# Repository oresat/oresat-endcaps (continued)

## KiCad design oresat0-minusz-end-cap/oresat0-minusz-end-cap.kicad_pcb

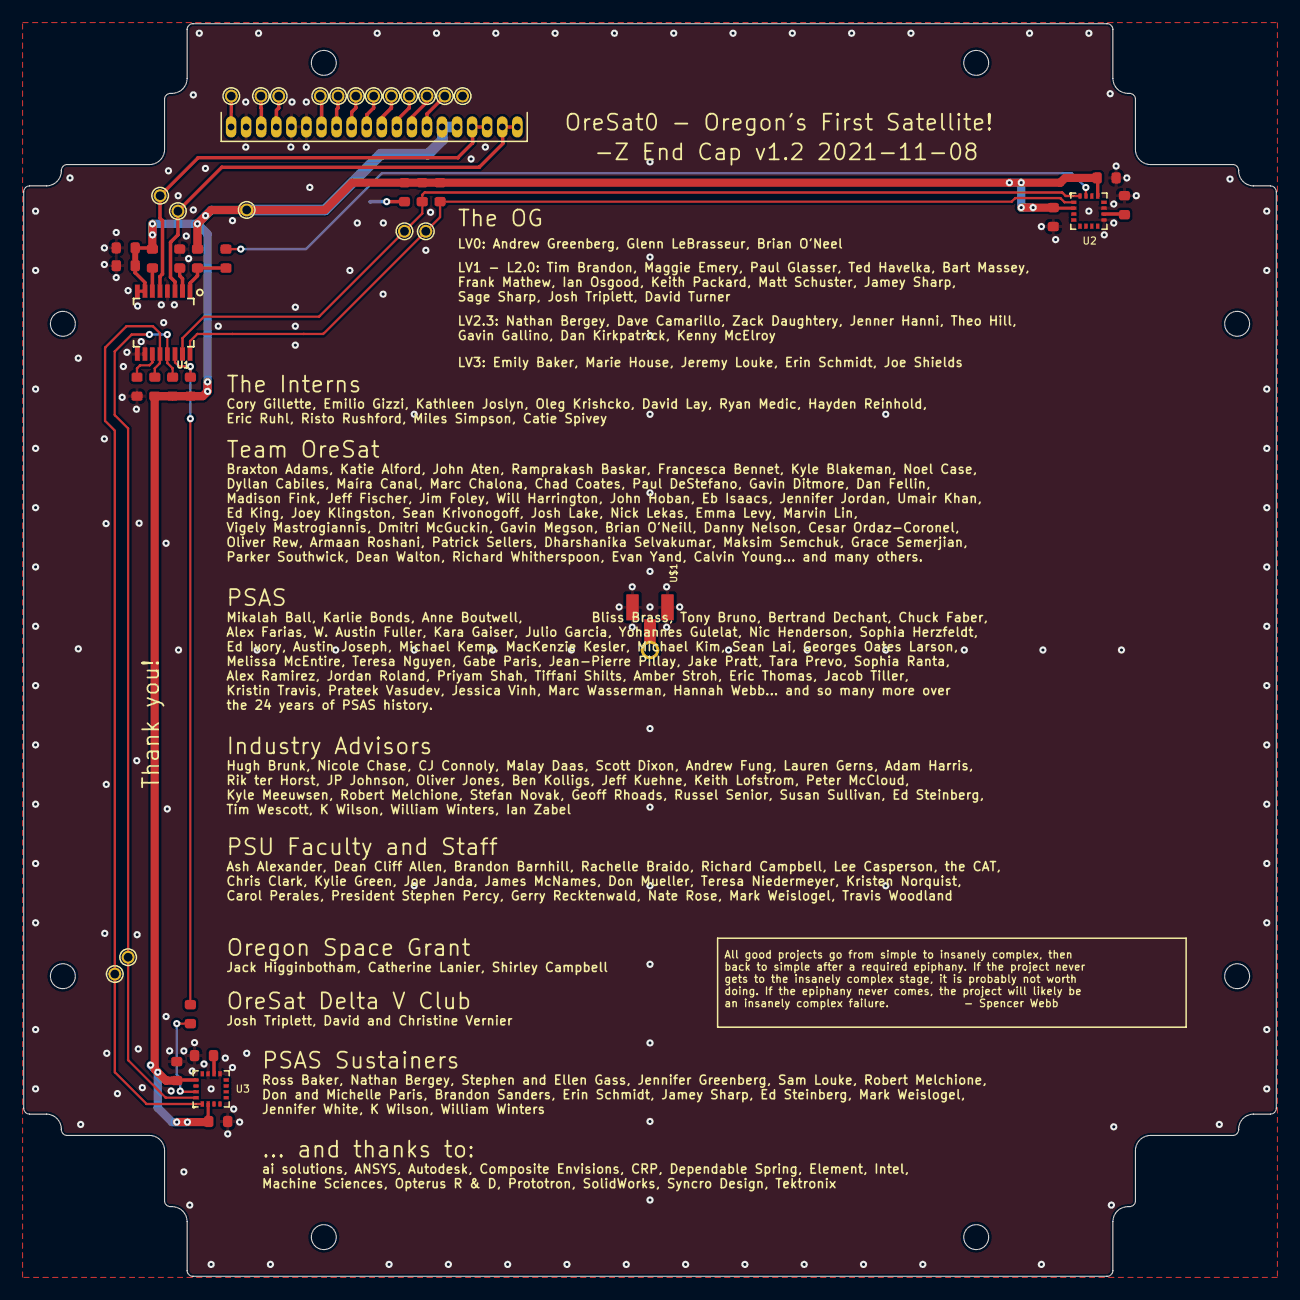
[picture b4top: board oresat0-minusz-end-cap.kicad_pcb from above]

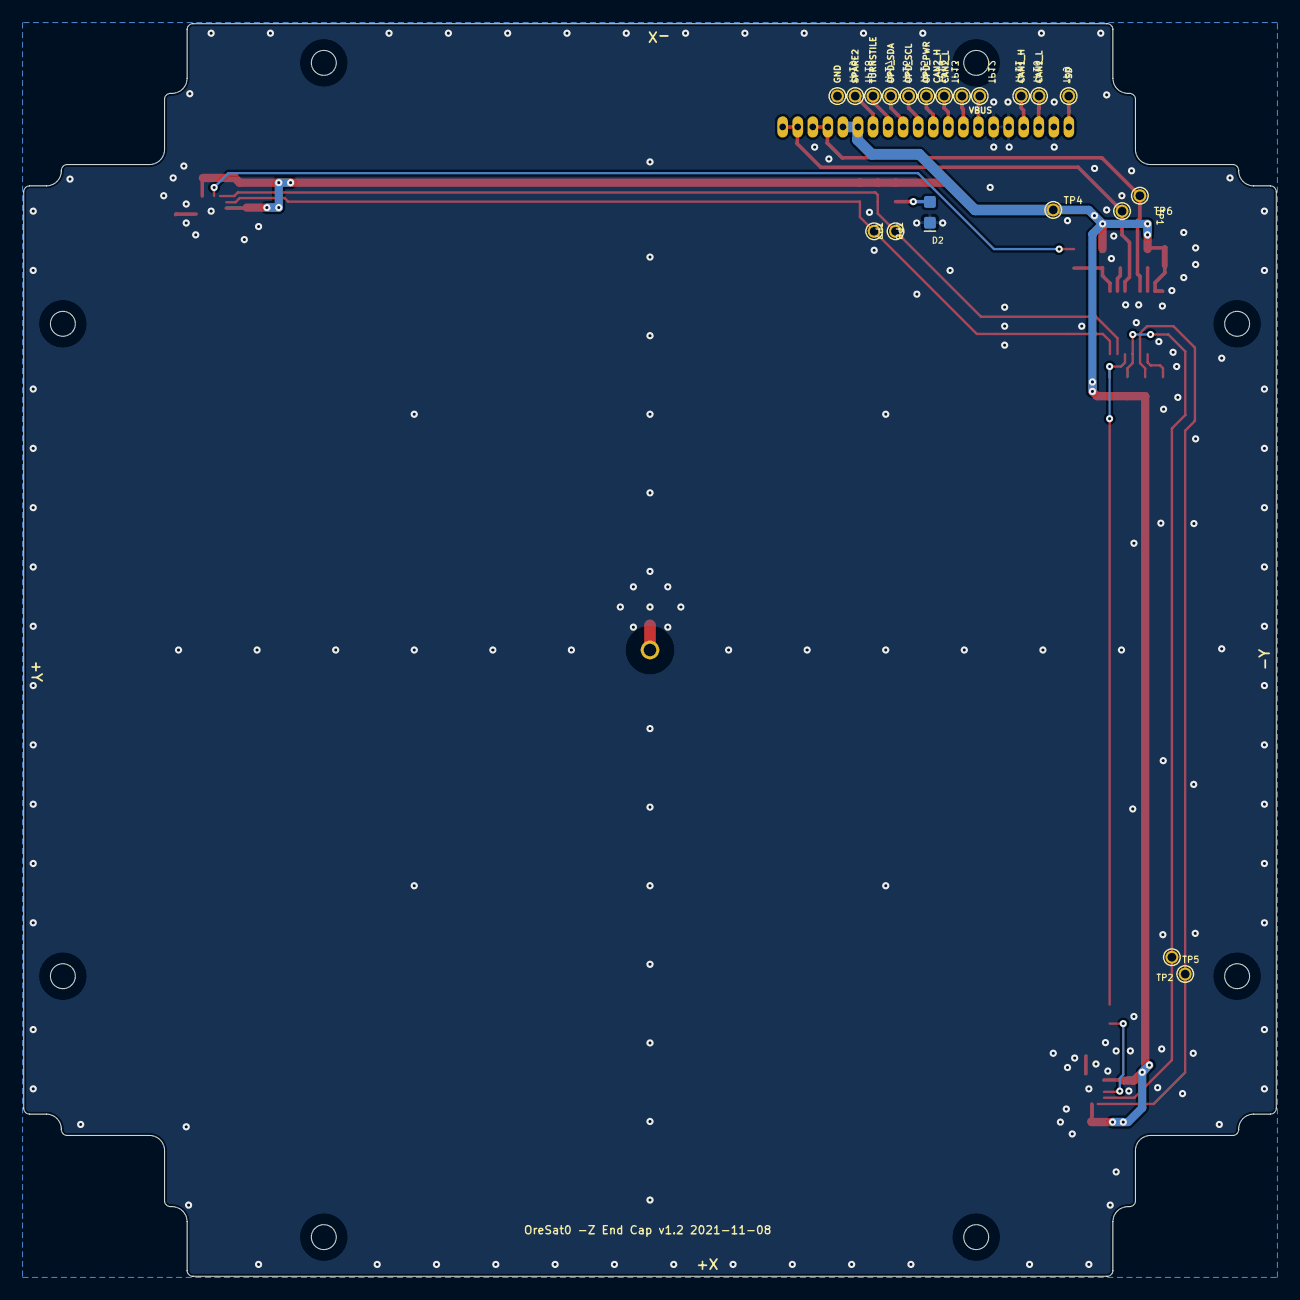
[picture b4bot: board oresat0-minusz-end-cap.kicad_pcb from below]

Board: 2 copper layers, 105.6 x 105.6 mm, 54 parts (3 on the bottom side), 30 nets.

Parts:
@HOLE0, @HOLE1, @HOLE2, @HOLE3, @HOLE4, @HOLE5, @HOLE6, @HOLE7: (no value)
C1, C2, C3, C7, C10: 100n; .0603-B-NOSILK
C4, C12, C13: 10u; .0603-B-NOSILK
D2: GREEN; LED-0603
E1: ANT-2.4-CPA; XDCR_ANT-2.4-CPA
J1: 6-104178-1
R1, R3, R4, R5, R6, R7, R8, R9, R10: 4.7k; .0603-B-NOSILK
R2: 2.7k; .0603-B-NOSILK
R11, R12: NP; .0603-B-NOSILK
TP1, TP2, TP3, TP4, TP5, TP6, TP7, TP8, TP9, TP10, TP11, TP12, TP13, TP14, TP15, TP16, TP17, TP18, TP19: TEST-POINT-LARGE-SQUARE; 1X01
U1: LTC4305; 16-SSOP
U2, U3: MMC5883MA; LGA-16(3X3)
U$1: U.FL-R-SMA; U.FL-R-SMT

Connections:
3.3V: C1.1, C2.2, C3.1, C4.1, C7.1, C10.1, J1.15, J1.16, R1.2, R2.2, R3.2, R4.2, R5.2, R6.2, R7.2, R8.2, TP4.1, U1.7, U1.8, U2.2, U2.13, U3.2, U3.13
CAN1_H: J1.4, TP11.1
CAN1_L: J1.3, TP10.1
CAN2_H: J1.9, TP14.1
CAN2_L: J1.8, TP13.1
GND: C1.2, C2.1, C3.2, C4.2, C7.2, C10.2, C12.2, C13.2, D2.C, J1.2, J1.5, J1.6, R9.1, R10.1, TP3.1, U1.4, U1.9, U1.10, U2.9, U2.11, U3.9, U3.11, U$1.2, U$1.3
I2C-SCL: J1.17, J1.18, TP1.1, U1.5
I2C-SDA: J1.19, J1.20, TP6.1, U1.3
unnamed: R8.1, U1.6
unnamed: C12.1, U3.10
unnamed: R1.1, R11.2, U1.14
unnamed: R3.1, R12.2, U1.1
unnamed: C13.1, U2.10
unnamed: R9.2, U1.2
unnamed: R10.2, U1.11
unnamed: R11.1, U3.15
unnamed: E1.1, U$1.1
unnamed: R12.1, U2.15
unnamed: D2.A, R2.1
OPD_PWR: J1.10, TP15.1
OPD_SCL: J1.11, TP16.1
OPD_SDA: J1.12, TP17.1
SCL1: R7.1, TP2.1, U1.12, U3.1
SCL2: R4.1, TP7.1, U1.16, U2.1
SDA1: R6.1, TP5.1, U1.13, U3.16
SDA2: R5.1, TP8.1, U1.15, U2.16
SPARE1-TURNSTYLE-DPLY: J1.13, TP18.1
SPARE2: J1.14, TP19.1
VBUS: J1.7, TP12.1
~SD: J1.1, TP9.1

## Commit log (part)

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2018-12-03 First try at a end card. Lots of stuff we don't need.
2018-12-03 Oh right, the bottom of the board.
2018-12-03 Updated version info on the board and readme, and added picture.
2018-12-03 Removed bad double title.
2018-12-19 Not done, but checking in anyway. Lots left to do, trying to figure out where things go.
2018-12-20 Removed SPS + uC blocks; only magnetometers remain on the end cap. Not great for future expandability, but moves uC to the end card where it's more useful.
2018-12-21 v1.0 done! All components on the inside to protect from The Spaces.
2018-12-21 Updated formatting.
2018-12-22 Updated outline based on new symmetrical end caps, decreased hole size but kept ground plane back.
2018-12-22 .. .and the -Z end cap. Again, just magnetometers.
2019-01-01 Added cutout for debug connector, update PNG.
2019-01-01 Added debug cutout to -Z end cap, and fixed README.
2019-02-25 Added updated keepouts for antennas; opened up helical opening.
2020-08-25 Added first version of OreSat0 end caps, though they are still not fully completed
2020-08-27 Added connector to backplane. Added NP resistors connecting magnetometer interrupts to i2c buffer alert inputs. Moved traces out of bstop area, and moved components away from the backplane. Changed b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
2020-08-27 Removed connector cutout from board outline. Increased restrict area for turnstile antenna. Changed some traces to the top layer to avoid the bstop area, and the new restrict area. Added NP resistors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
2020-08-28 v1.0 end caps for OreSat0!
2020-08-28 Moved SCL1 and SDA1 traces to avoid tstop area.
2020-08-29 Updated DXF and board outline. Also cleaned up tNames and Bplace layers around backplane connector.
2020-08-29 Added BOMs and updated attributes for OreSat0 + and - Z end caps.
2020-09-11 Fixed mysterious blank plus z BOM. Also added date and notes fields to minus z BOM.
2021-03-28 To begin redoing the +Z end cap board, I took the dimension layer from the 9-10-20 version of the board file and replaced it with the new DXF from Hayden Reinhold.
2021-03-28 I updated the dxf and dimension layers on the oresat 0 +Z end cap board. I also cleared all the DRC errors.
2021-04-09 New +Z end cap with larger cutout for turnstile.
    New -Z end cap with amazing artwork from Jennifer and thank yous.
2021-10-21 New pretty OreSat0 end cap, now with updated launch provider.
2021-11-09 Updated some of the back matter.
2021-11-10 bplace updates
    CRP & SP added to bplace layer
2022-07-25 Moved endcaps to KiCad
2022-07-25 Moved the oresat0 +z endcap to KiCad
2022-07-27 Moved OreSat0 -z to KiCad
2022-07-27 Added generic -z end cap
2023-02-06 Clean up directory structure to reflect per-satellite end caps
2023-02-12 Renamed to satellite name folders as per other repos
2023-02-17 Adds DXF of latest +Z end cap.
2023-02-17 Update oresat0.5 plusz end cap file names, and copied oresat0 plusz design, since old 0.5 design was ooooooold
2023-02-18 Updated oresat0.5 +Z board outline
2023-02-18 Adding DXF of OreSat0.5 -Z endcap
2023-02-18 Small fixes to oresat0.5 +Z end cap, and added new DXF to -Z cap. Also renamed minusz cap to oresat0.5-minusz
2023-02-19 Updated both oresat0.5 end caps. Fixed layout, and added patch antennas
2023-02-19 Updated both OreSat0.5 end caps and cleaned up errors
2023-02-19 OreSat0.5 end caps design review fixes
2023-02-21 Archiving Oresat0 +Z End Cap. Got rid of bad KiCAD import, made PDFs for future use.
2023-02-21 Archiving OreSat0 -Z end cap, with pretty PNGs and PDFs.
2023-02-21 Updated .gitignore for archive folder, updated readme, and killed old useless eagle file.
2023-02-21 Remove unused files; updated PCB with CAM settings.
2023-02-21 Removed unused files, added CAM settings to PCB file.
2023-02-21 Updated CAM settings in PCB
2023-02-21 Forgot silkscreen in CAM. Fixed.
2023-02-21 Added white silkscreen square for board number! Super critical! :)
2023-07-06 Adding DXF of OreSat0 -Z end cap.
2023-09-03 Updated end caps
2023-09-11 Updated magnetometer symbol
2023-09-11 Updated mounting holes
2023-09-15 OreSat0.5 -Z end cap. Updated to latest KiCAD, fixed lack of holes for lens holder, and removed solder mask from around screw heads.
2023-09-15 Oresat0.5 +Z End Cap. Still some weird library issues, but skipping for now.
2023-12-21 Upgrades OreSat0.5 +Z End Cap to v1.2 -- fits the new deployer, and cleans up a bunch of library issues.
2024-02-03 corrected board outline for OreSat 0.5 +z endcap
2024-02-29 Small changes to schematic, mostly comments.
2024-03-04 updated mmc5883 magnetometer to mmc5983 for both OreSat 0.5 +Z and -Z endcaps
2024-03-20 moved endcap harwin connectors on both +/-Z endcaps per move in Onshape
2024-03-21 Oresat 0.5 +z end cap v1.3 ready for ordering!
2024-03-21 OreSat 0.5 Endcaps (+Z v1.3 and -Z v1.2) ready for ordering, reviewed -Z endcap, made small library and neatness changes to +Z endcap
2024-04-08 Fixed issues 5 and 6 -- weird 4.7k values everywhere, missing libraries, and used no-place to indicate actual no place components.
2024-04-15 Added note on which MAG was which for firmware (PZ1 - MZ2).
2024-05-06 More information on end cap RF, including coax jumper for end cap.
2024-05-07 Updated BOM to include MFR/MPN/etc.
2024-05-08 Fixed BOM.
2024-12-12 Added KiCAD 8 import of OreSat0 +Z End Cap v1.1. Still needs lots of work to swich to KiCAD components, and get the schematic/layout synchronized.
2026-01-26 minus z endcap schematic & pcb w/ PNI rm3100 mag
    Beginning of rework w PNI rm3100
2026-01-31 RM 3100 board layout
    Round 1 - awaiting design review. Some issues with GND pads; DRC is clean, but looks weird. Debating if U1 needs to be further in the corner, therefore change its layout completely.
2026-02-01 Polishing the schematic and layout
    Cleaned up ERCs, lots of OCD polishing for no reason, added 3.3V zone, cleaned up 3.3V routing.
2026-02-01 Fix BOM and add 3D of antenna.
2026-02-05 Plus Z endcap - new dfx and rm3100 magnetometers.
    Routing complete. DRC warnings and errors about the antenna footprint. Labelled pads as unspecified (neither through hole or SMD) and still getting a warning. Other warnings about silkscreen being cl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
2026-02-06 New -Z DFX
    Added new DFX to edge.cuts and User.comments. Antenna footprint warning - juts out over cut.
2026-02-12 Added 3D models and fixed fab des
    3D models of antenna patch (-Z) and M55 connector & magIc2 chip on both boards.
2026-03-11 +Z End Cap ready for fab and assembly.
    Schematic: Made RM3100 symbol better, cleaned up schematic, added variable strings, DRC'd,
    added fiducials
    Layout: Added fiducials, cleaned up polygons, rerouted signals too close to the edge,
    Fixed the connector to the +Z End Card (it was wrong in so many ways), added all the
    3D models to things, fixed the Makefile to use STEP not VRML files, reset the footprint
    libraries Added the correct and latest DXF outline. Removed old DXF and old crusty
2026-03-11 Added note on patch antenna
2026-03-11 Added Oresat logo, updated PSAS logo!
2026-03-11 Tweak to logo files for DRC
2026-03-11 Better doc notes, including on U.FL to U.FL cabling
2026-04-10 Update OreSat1 +Z End Cap, but no new build, no substantial change from v1.0, just updated makefile, readme, and some library footprint updates.
2026-04-10 Add beginnings of the ESI -Z End Cap
2026-04-10 Added customized version of the +Z end cap for ESI
2026-04-11 New DFX & reposition GPS 7 magnetometers
2026-04-23 New DFX (bias left) & rerouted accordingly. Made pretty. Done?
2026-04-23 ESI -Z end cap, with build files, final answer
2026-04-23 update .gitignore for kicad 10
